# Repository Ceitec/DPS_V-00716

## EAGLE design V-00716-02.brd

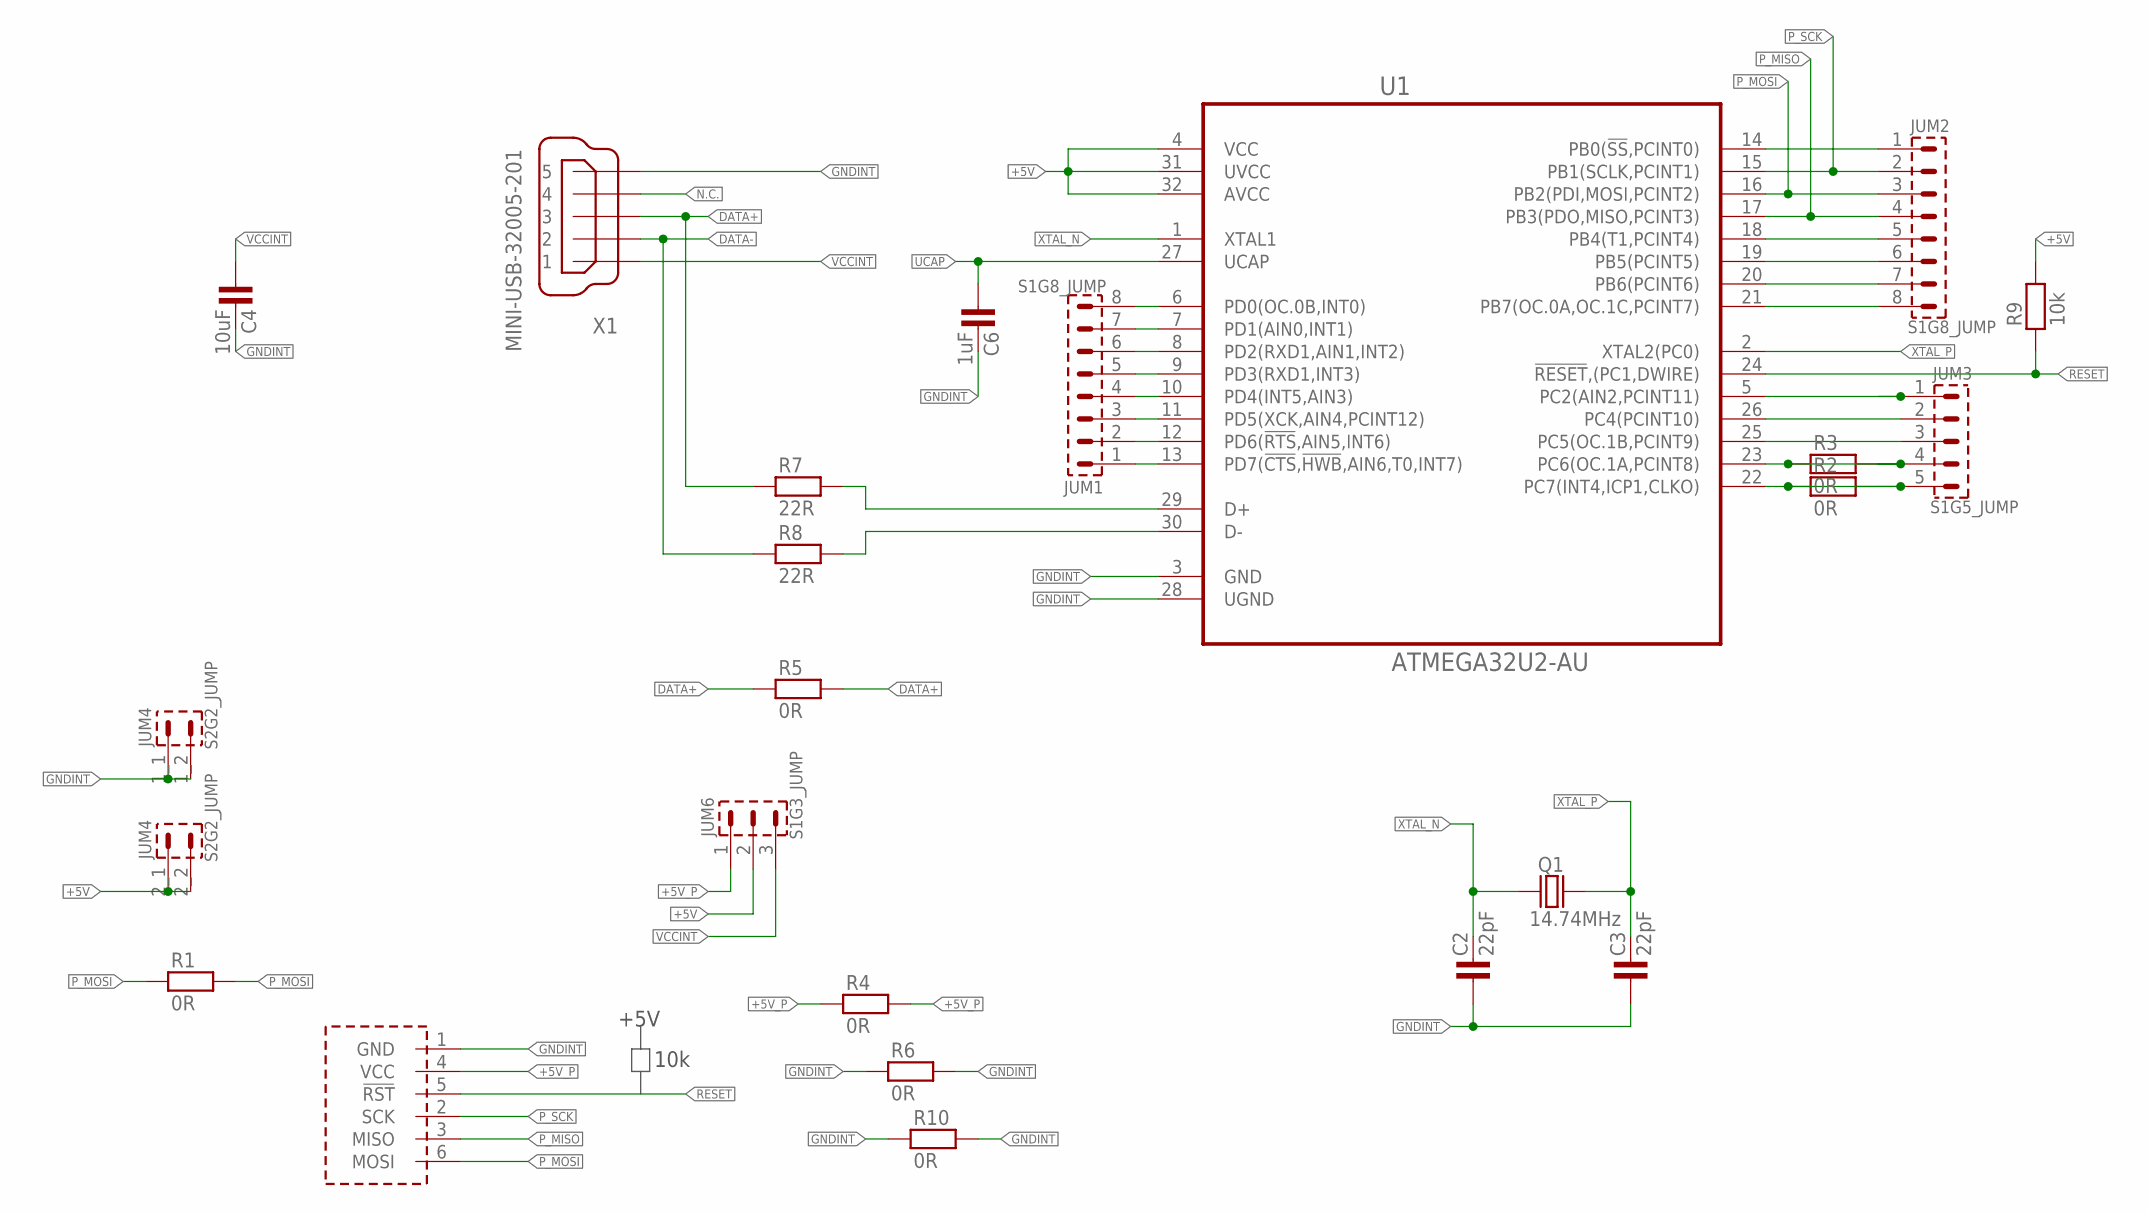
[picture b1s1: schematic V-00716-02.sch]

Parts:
C2, C3: 22pF; 0805
C4: 10uF; 1206
C6: 1uF; 1206
JUM1, JUM2: S1G8_JUMP; S1G8_JUM
JUM3: S1G5_JUMP; S1G5_JUM
JUM4: S2G2_JUMP; S2G2_JUM
JUM6: S1G3_JUMP; S1G3_JUM
Q1: 14.74MHz; HC-49U
R1, R2, R3, R4, R5, R6, R10: 0R; 1206
R7, R8: 22R; 1206
R9: 10k; 1206
U1: ATMEGA32U2-AU; QFP80P900X900X120-32N
U$1: AVR_PROG_SPI; PSH02-06P
X1: MINI-USB-32005-201; 32005-201

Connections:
+5V: JUM4.2_1 (1), JUM4.2_2 (2), JUM6.2, R9.2, U1.4 (VCC), U1.31 (UVCC), U1.32 (AVCC)
+5V_P: JUM6.1, R4.1, R4.2, U$1.4 (VCC)
DATA+: R5.1, R5.2, R7.1, X1.3
DATA-: R8.1, X1.2
GNDINT: C2.1, C3.1, C4.2, C6.2, JUM4.1_1 (1), JUM4.1_2 (2), R6.1, R6.2, R10.1, R10.2, U1.3 (GND), U1.28 (UGND), U$1.1 (GND), X1.5
unnamed: JUM1.1, U1.13 (PD7(!CTS,!HWB,AIN6,T0,INT7))
unnamed: R7.2, U1.29 (D+)
unnamed: JUM1.2, U1.12 (PD6(!RTS,AIN5,INT6))
unnamed: JUM1.3, U1.11 (PD5(XCK,AIN4,PCINT12))
unnamed: JUM1.4, U1.10 (PD4(INT5,AIN3))
unnamed: JUM1.5, U1.9 (PD3(RXD1,INT3))
unnamed: JUM1.6, U1.8 (PD2(RXD1,AIN1,INT2))
unnamed: JUM1.7, U1.7 (PD1(AIN0,INT1))
unnamed: JUM1.8, U1.6 (PD0(OC.0B,INT0))
unnamed: JUM3.1, U1.5 (PC2(AIN2,PCINT11))
unnamed: JUM3.2, U1.26 (PC4(PCINT10))
unnamed: R8.2, U1.30 (D-)
unnamed: JUM3.3, U1.25 (PC5(OC.1B,PCINT9))
unnamed: JUM3.4, R3.1, R3.2, U1.23 (PC6(OC.1A,PCINT8))
unnamed: JUM3.5, R2.1, R2.2, U1.22 (PC7(INT4,ICP1,CLKO))
unnamed: JUM2.1, U1.14 (PB0(!SS,PCINT0))
unnamed: JUM2.5, U1.18 (PB4(T1,PCINT4))
unnamed: JUM2.6, U1.19 (PB5(PCINT5))
unnamed: JUM2.7, U1.20 (PB6(PCINT6))
unnamed: JUM2.8, U1.21 (PB7(OC.0A,OC.1C,PCINT7))
N.C.: X1.4
P_MISO: JUM2.4, U1.17 (PB3(PDO,MISO,PCINT3)), U$1.3 (MISO)
P_MOSI: JUM2.3, R1.1, R1.2, U1.16 (PB2(PDI,MOSI,PCINT2)), U$1.6 (MOSI)
P_SCK: JUM2.2, U1.15 (PB1(SCLK,PCINT1)), U$1.2 (SCK)
RESET: R9.1, U1.24 (!RESET,(PC1,DWIRE)), U$1.5 (!RST)
UCAP: C6.1, U1.27 (UCAP)
VCCINT: C4.1, JUM6.3, X1.1
XTAL_N: C2.2, Q1.1, U1.1 (XTAL1)
XTAL_P: C3.2, Q1.2, U1.2 (XTAL2(PC0))

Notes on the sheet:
+5V
10k

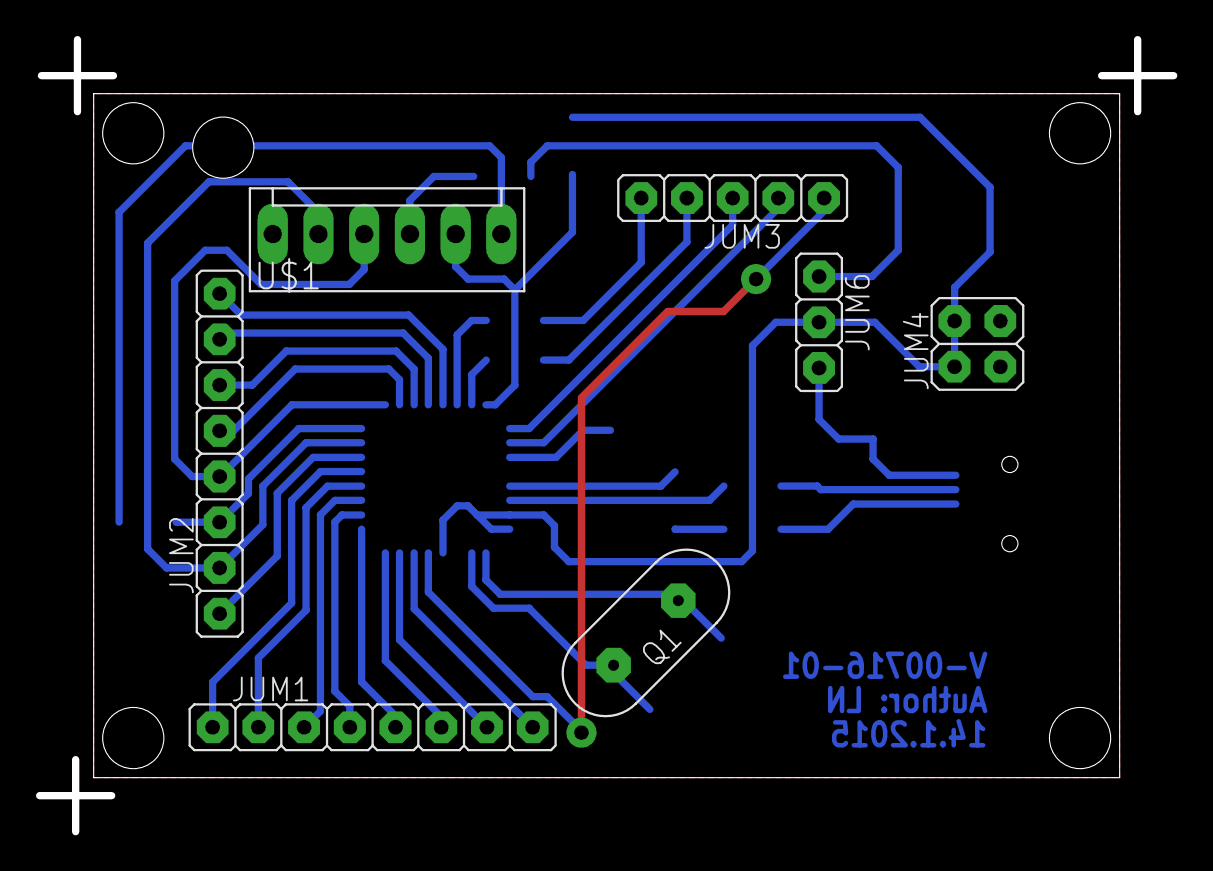
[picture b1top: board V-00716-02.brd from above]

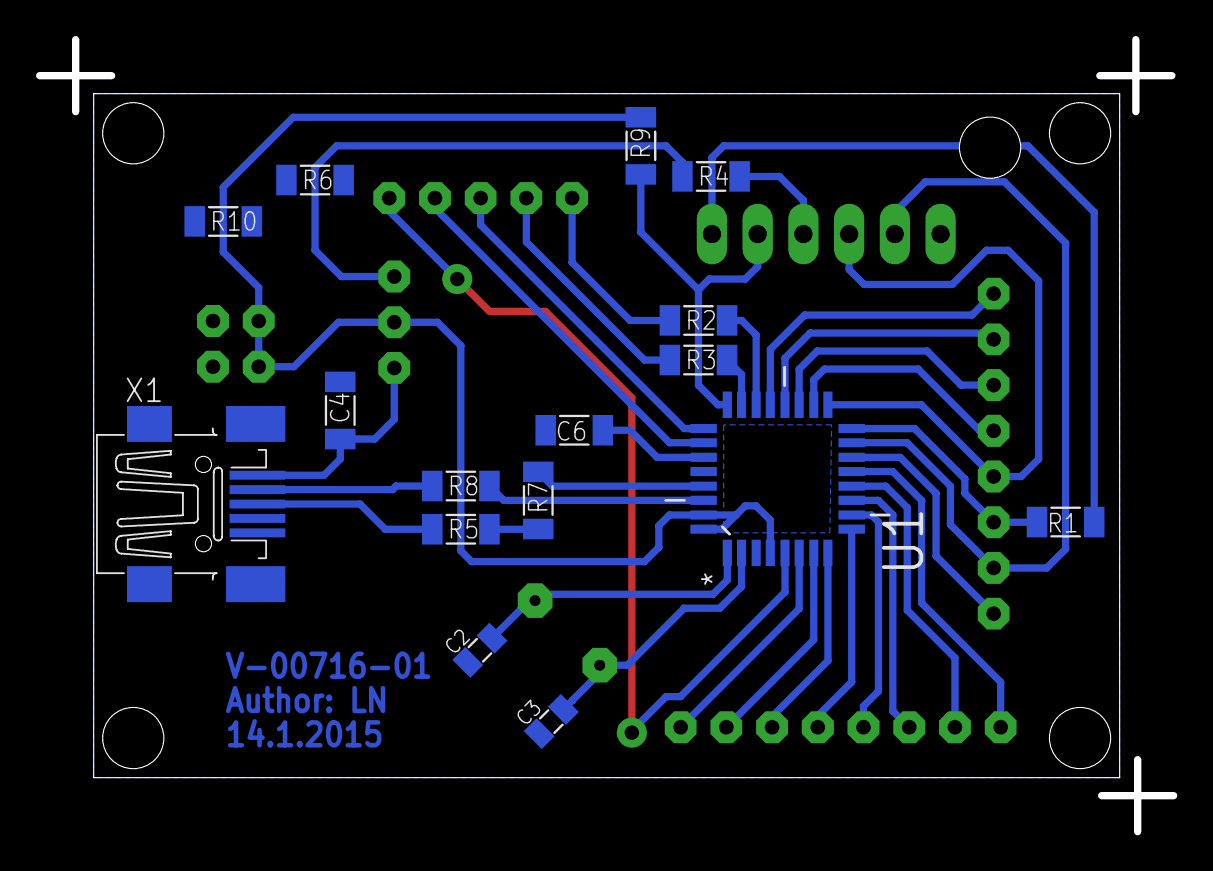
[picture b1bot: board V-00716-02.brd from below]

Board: 2 copper layers, 63.0 x 44.0 mm, 23 parts (16 on the bottom side), 33 nets.

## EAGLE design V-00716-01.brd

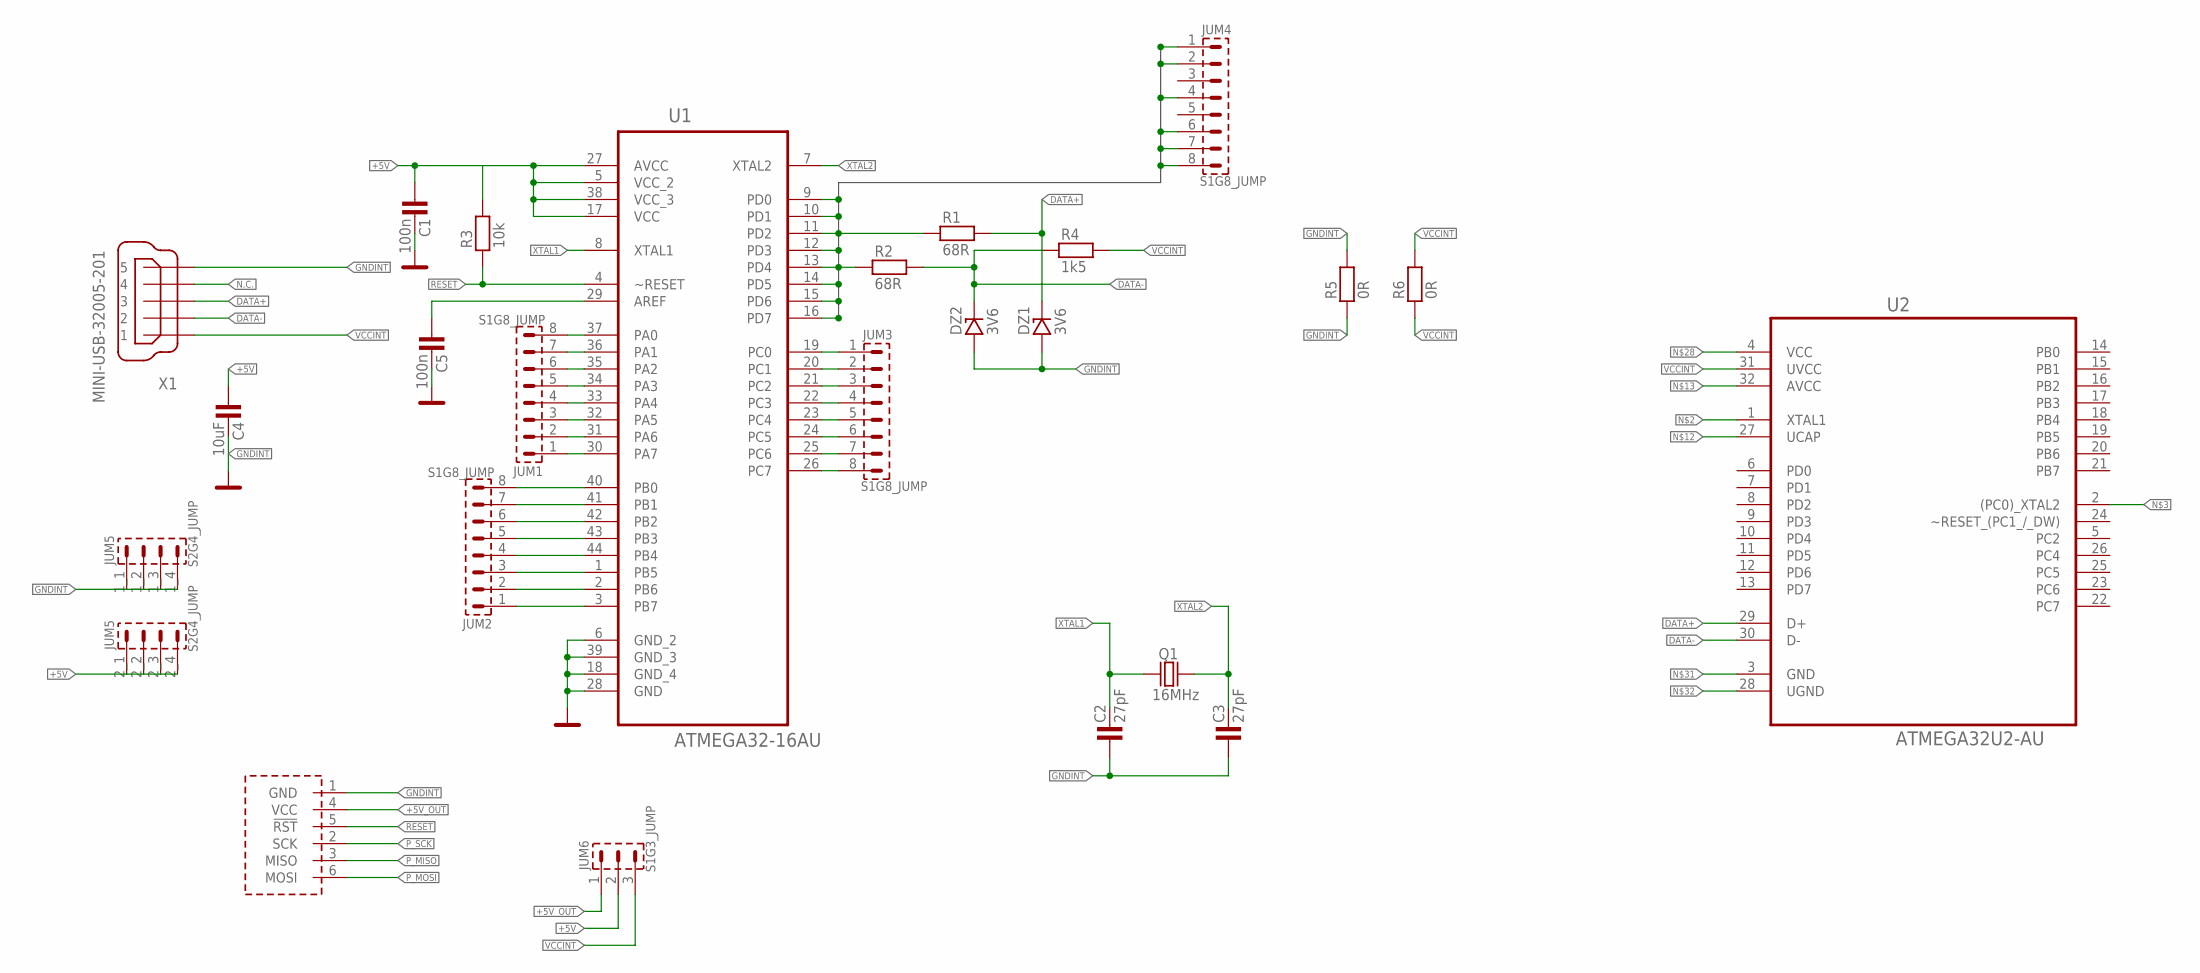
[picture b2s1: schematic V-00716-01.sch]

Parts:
C1, C5: 100n; 1206
C2, C3: 27pF; 0805
C4: 10uF; 1206
DZ1, DZ2: 3V6; SOD-80
JUM1, JUM2, JUM3, JUM4: S1G8_JUMP; S1G8_JUM
JUM5: S2G4_JUMP; S2G4_JUM
JUM6: S1G3_JUMP; S1G3_JUM
Q1: 16MHz; HC-49U
R1, R2: 68R; 1206
R3: 10k; 1206
R4: 1k5; 1206
R5, R6: 0R; 1206
U1: ATMEGA32-16AU; QFP80P1200X1200X120-44N
U2: ATMEGA32U2-AU; QFP80P900X900X120-32N
U$1: AVR_PROG_SPI; PSH02-06P
X1: MINI-USB-32005-201; 32005-201

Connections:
+5V: C1.1, C4.1, JUM5.2_1 (1), JUM5.2_2 (2), JUM5.2_3 (3), JUM5.2_4 (4), JUM6.2, R3.2, U1.5 (VCC_2), U1.17 (VCC), U1.27 (AVCC), U1.38 (VCC_3)
+5V_OUT: JUM6.1, U$1.4 (VCC)
DATA+: DZ1.K, R1.2, U2.29 (D+), X1.3
DATA-: DZ2.K, R2.2, R4.1, U2.30 (D-), X1.2
GNDINT: C1.2, C2.1, C3.1, C4.2, C5.2, DZ1.A, DZ2.A, JUM5.1_1 (1), JUM5.1_2 (2), JUM5.1_3 (3), JUM5.1_4 (4), R5.1, R5.2, U1.6 (GND_2), U1.18 (GND_4), U1.28 (GND), U1.39 (GND_3), U$1.1 (GND), X1.5
unnamed: C5.1, U1.29 (AREF)
unnamed: JUM1.1, U1.30 (PA7)
unnamed: JUM1.2, U1.31 (PA6)
unnamed: JUM1.3, U1.32 (PA5)
unnamed: JUM1.4, U1.33 (PA4)
unnamed: JUM1.5, U1.34 (PA3)
unnamed: JUM1.6, U1.35 (PA2)
unnamed: JUM1.7, U1.36 (PA1)
unnamed: JUM1.8, U1.37 (PA0)
unnamed: JUM2.4, U1.44 (PB4)
unnamed: JUM2.5, U1.43 (PB3)
unnamed: JUM2.6, U1.42 (PB2)
unnamed: JUM2.7, U1.41 (PB1)
unnamed: JUM2.8, U1.40 (PB0)
unnamed: JUM3.1, U1.19 (PC0)
unnamed: JUM3.2, U1.20 (PC1)
unnamed: JUM3.3, U1.21 (PC2)
unnamed: JUM3.4, U1.22 (PC3)
unnamed: JUM3.5, U1.23 (PC4)
unnamed: JUM3.6, U1.24 (PC5)
unnamed: JUM3.7, U1.25 (PC6)
unnamed: JUM3.8, U1.26 (PC7)
N.C.: X1.4
PD0: JUM4.1, U1.9 (PD0)
PD1: JUM4.2, U1.10 (PD1)
PD2: R1.1, U1.11 (PD2)
PD3: JUM4.4, U1.12 (PD3)
PD4: R2.1, U1.13 (PD4)
PD5: JUM4.6, U1.14 (PD5)
PD6: JUM4.7, U1.15 (PD6)
PD7: JUM4.8, U1.16 (PD7)
P_MISO: JUM2.2, U1.2 (PB6), U$1.3 (MISO)
P_MOSI: JUM2.3, U1.1 (PB5), U$1.6 (MOSI)
P_SCK: JUM2.1, U1.3 (PB7), U$1.2 (SCK)
RESET: R3.1, U1.4 (~RESET), U$1.5 (!RST)
VCCINT: JUM6.3, R4.2, R6.1, R6.2, U2.31 (UVCC), X1.1
XTAL1: C2.2, Q1.1, U1.8 (XTAL1)
XTAL2: C3.2, Q1.2, U1.7 (XTAL2)

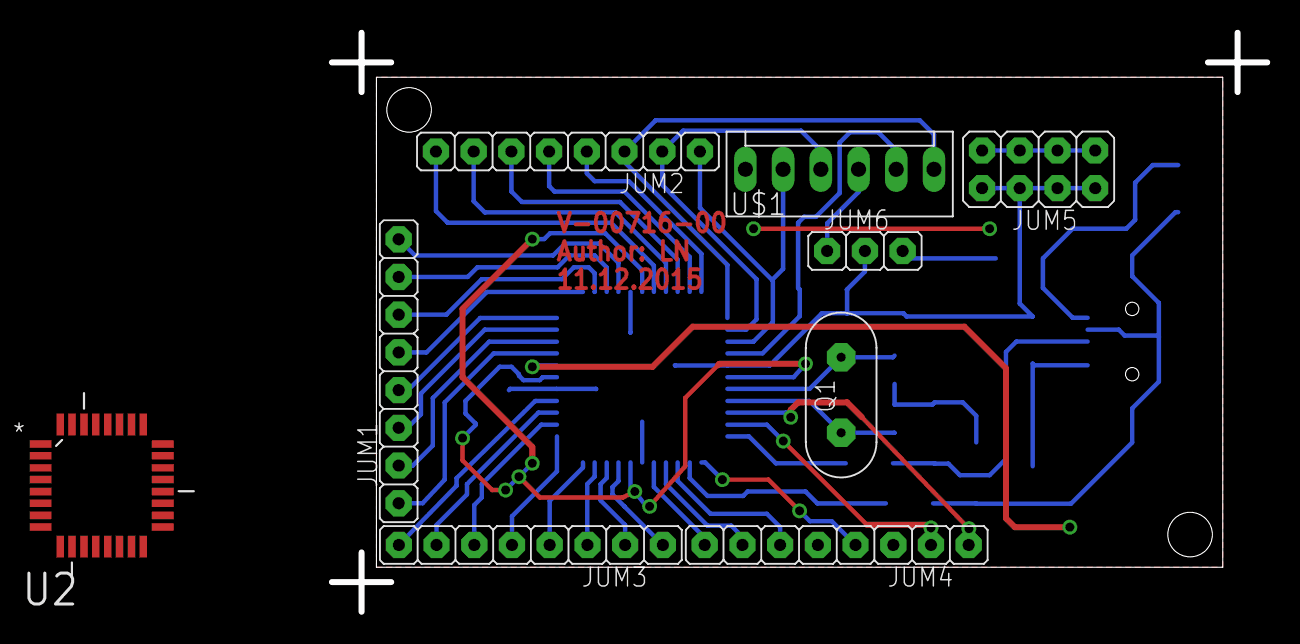
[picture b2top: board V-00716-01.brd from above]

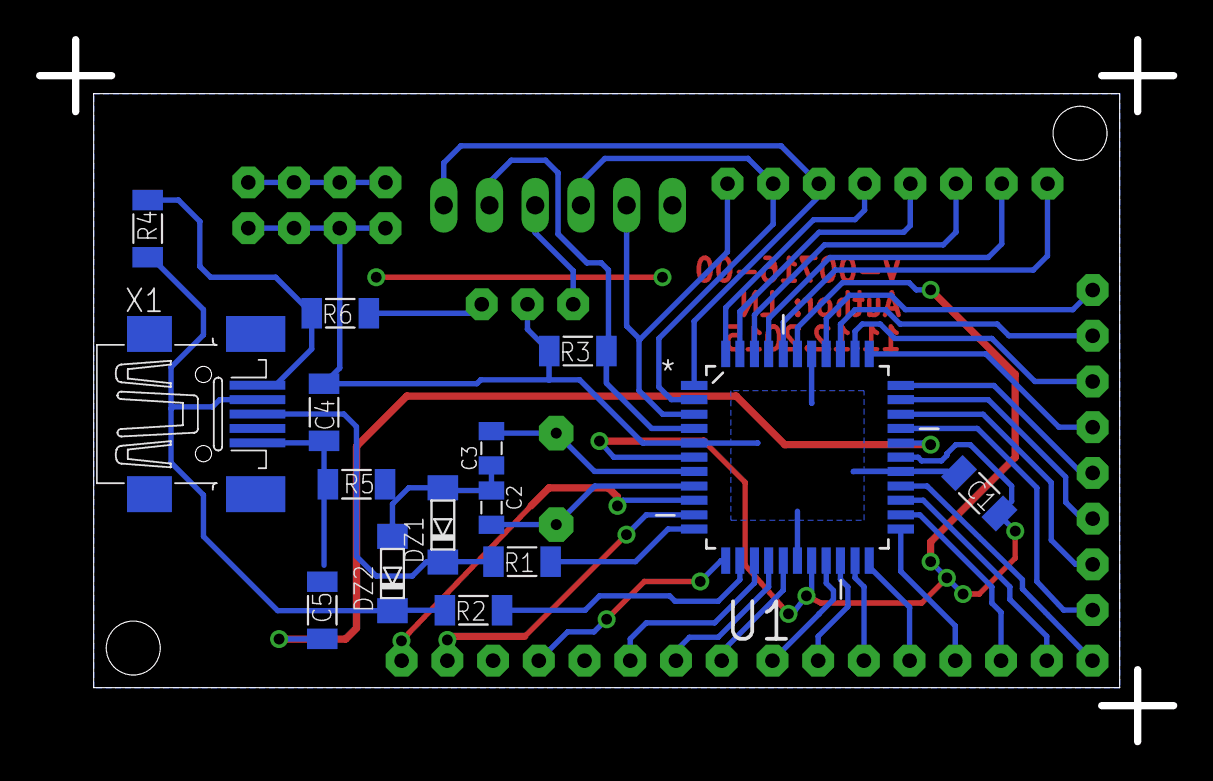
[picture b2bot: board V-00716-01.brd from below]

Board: 2 copper layers, 63.0 x 39.0 mm, 24 parts (15 on the bottom side), 42 nets.

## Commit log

2015-11-30 :tada: Added .gitattributes & .gitignore files
2015-11-30 USB HID
2015-12-11 v1.1.0.1
2016-01-13 v1.1.0.2
    Uprava pro vyrobu v Gatemě
2016-01-21 v.2.0.0
    Nová verze z jiným mcu atmega32u2
2016-02-10 v.2.1
    Upravena verze + udelana verze 02 s upravy chyb

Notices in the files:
parts and their libraries:
Copyright (C) PaJa 2001-2014
Copyright (C) PaJa 2011-2014
